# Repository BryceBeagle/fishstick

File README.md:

# fishstick
USB Dongle/adapter for gamecube controllers

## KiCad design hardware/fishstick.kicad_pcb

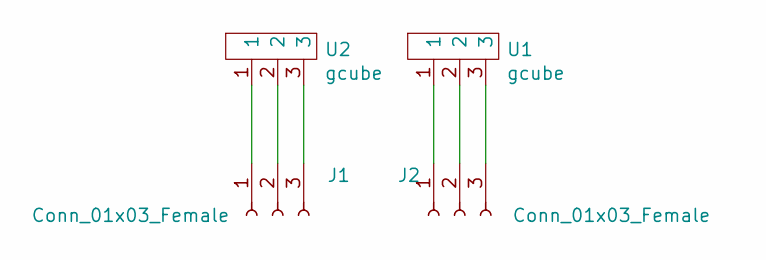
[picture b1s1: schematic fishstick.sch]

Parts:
J1, J2: Conn_01x03_Female; PinHeader_1x03_P2.54mm_Vertical
U1, U2: gcube; SOIC-3

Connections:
unnamed: J1.1, U2.1
unnamed: J1.2, U2.2
unnamed: J1.3, U2.3
unnamed: J2.1, U1.1
unnamed: J2.2, U1.2
unnamed: J2.3, U1.3

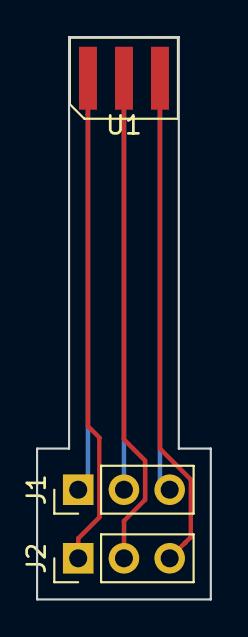
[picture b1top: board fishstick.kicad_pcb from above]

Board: 2 copper layers, 9.7 x 31.2 mm, 4 parts (1 on the bottom side), 6 nets.

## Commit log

2019-08-31 Initial commit of nested timer setup
2019-09-01 prepared directory for repository
2021-04-20 Switch to using rust
2022-01-29 Test bluepill flash light
2022-01-29 added intellij files
2022-01-29 added intellij rust run configurations
2022-01-29 added intellij items again
2022-01-29 newline dad
2022-01-29 removed run configs that contain absolute paths
2022-01-30 Add IntelliJ files and configuration (#1)
2022-01-30 added jet brains run configurations
2022-01-30 added run configurations
2022-01-30 new line youre welcome dad
2022-01-30 Add IntelliJ run configurations (#3)
2022-04-18 Rename project in `Cargo.toml` to `fishstick`
2022-04-18 Rename project in `Cargo.toml` to `fishstick` (#5)
2022-04-23 Update dependencies
    Resolves #6
2022-04-23 Update dependencies (#7)
2022-04-23 Add `bitvec` as a dependency
    Resolves #8
2022-04-23 Add `bitvec` as a dependency (#9)
    Resolves #8
2022-04-28 changed test code to use onboard LED instead of externally connected LEDs
2022-04-28 Fix name of binary in `Download and Run` run configuration
    Resolves #10
2022-04-28 Fix name of binary in `Download and Run` run configuration (#12)
2022-04-28 added newline
2022-04-28 changed test code to use onboard LED instead of externally connected LEDs (#11)
2022-05-08 Rename CLion project to `fishstick`
    Resolves #14
2022-05-08 Rename CLion project to `fishstick` (#15)
    Resolves #14
2022-07-23 Enhanced project structure for embedded software
    Resolves #16
2022-07-23 Enhanced project structure for embedded software (#17)
    Resolves #16
2022-07-23 switched main.rs to lib.rs and improved structure
2022-07-23 NEWLINE
2022-07-23 Switch `fishstick` crate from `main.rs` to `lib.rs` (#19)
2022-07-24 improved joybus method structure
2022-07-24 ignore .idea shelf
2022-07-24 Ignore `.idea` shelf (#26)
2022-07-24 Switch build run configuration to use `nightly` channel
    commit-id:3232d078
2022-07-24 Add missing space in `stm32` `Cargo.toml`
    Resolves #29
    commit-id:41f75ff2
2022-07-24 Use lowercase name for `build` run configuration
    commit-id:a68664fc
2022-07-24 Improve `joybus` method structure (#24)
2022-07-24 Add a `rust-toolchain.toml` to `fishstick` crate with nightly channel
    commit-id:3232d078
2022-07-24 Set `software/fishstick/tests` as a test source folder in CLion
    commit-id:5b14ba2b
2022-07-25 Use lowercase name for `build` run configuration (#31)
2022-07-25 Add missing space in `stm32` `Cargo.toml` (#33)
2022-07-25 Set `software/fishstick/tests` as a test source folder in CLion (#34)
2022-07-25 Stop using `nightly` channel for `stm32` crate
    Resolves #37
    commit-id:c3aac06d
2022-07-25 Stop using `nightly` channel for `stm32` crate (#38)
2022-07-25 implemented `Joybus` `send_receive` within trait itself and updated `Controller`
2022-07-25 switch to `pub mod joybus` since we are including everything already
2022-07-25 Revert "switch to `pub mod joybus` since we are including everything already"
    This reverts commit 24748f82f5f898f62dffec190a583538e391e744.
2022-07-25 added back `exists` method to `Controller`
2022-07-25 renamed `get_state` method to be more clear
2022-07-25 reverted to old `Controller` code as a next level abstraction for `Joybus`
2022-07-26 Implemented `Joybus` `send_receive`. Updated `Controller`. (#40)
2022-07-26 renamed stm32 crate to match specific device
2022-07-26 update `Cargo.lock`
2022-07-27 Rename `stm32` crate to match specific device (`stm32f103`) (#42)
2022-07-27 added `stm32f401` crate and dependencies
2022-07-27 changed run config parameters
2022-07-27 remove clippy pragma
2022-07-27 rename blackpill .cfg file
2022-07-27 remove errant comment
2022-07-28 rename run configurations; rename stlink config
    commit-id:8b618238
2022-07-28 un-rename stlink config
    commit-id:5cc6404f
2022-07-28 Add `stm32f401` crate and dependencies (#46)
2022-07-28 Bare deployment for `stm32f103` board
    Resolves #47
    Resolves #48
2022-07-28 Bare deployment for `stm32f103` board (#49)
2022-07-30 `fishstick-stm32f103` dependency on `fishstick`
    This makes the `fishstick-stm32f103` have a real dependency on the core
    `fishstick` crate
    Resolves #51
2022-07-30 `fishstick-stm32f103` dependency on `fishstick` (#52)
    This makes the `fishstick-stm32f103` have a real dependency on the core
    `fishstick` crate
    Resolves #51
2022-07-30 Sanity-check test for `fishstick` that runs on host machine
    Even though the test requires the `std` crate, the hardware crates can still use it at runtime.
    Resolves #53
2022-07-30 GitHub Linguist override for Linker Script files
    Resolves #50
2022-07-30 Sanity-check test for `fishstick` that runs on host machine (#54)
2022-07-30 GitHub Linguist override for Linker Script files (#55)
2022-11-05 remove nightly requirement
2022-11-05 use `panic_rtt_target` instead of `panic_halt`
2022-11-05 no test check to get rid of rust-analyzer error
2022-11-05 added `Embed.toml` for `cargo embed`
2022-11-05 added comment to explain rust-analyzer silence
2022-11-05 `cargo embed` setup for `stm-32f401` crate (#56)
2022-11-05 base for spi writing
2022-11-07 clock timing to fix weird SPI clock errors
2022-11-07 improved clock timing
2022-11-07 allow dead code on test message
2023-07-03 initial impl of a disgusting PWM DMA output
2023-08-12 Drop support for stm32f103
    Resolves #59
2023-08-12 Unpin and upgrade all dependency versions
    We can rely on the lockfile to keep the exact versions consistent
    Resolves #58
2023-08-12 DMA thing
2023-08-17 Drop support for stm32f103 (#60)
2023-08-20 update again
2023-08-20 fix unicode-ident checksum
2023-08-21 Switch logging from `rtt_target` to `defmt`
    Resolves #62
2023-08-26 Unpin and upgrade all dependency versions (#61)
2023-08-26 Replace all `stm32f401` configuration with `stm32f411` configuration
    Resolves #64
2023-08-26 Start using `embassy` framework
    Note that this introduces an issue where flashing requires using `BOOT0` and `NRST`
    Resolves #66
2023-10-01 Switch logging from `rtt_target` to `defmt` (#63)
2023-10-01 Replace `stm32f401` in run configuration with `stm32f411`
2023-10-01 Replace all `stm32f401` config with `stm32f411` config (#65)
2023-10-01 Start using `embassy` framework (#67)
2023-12-30 Bump all package versions
    Resolves #68
2023-12-30 Bump all package versions (#69)
    Resolves #68
2023-12-30 added `embassy-usb`, `futures` and updated dependencies
2023-12-30 added `embassy-usb`, `futures` and updated dependencies (#71)
2023-12-30 Working example of loopback over USB
    Plug in USBC and open Arduino Serial monitor. Anything sent over serial gets sent back in uppercase
2024-01-22 upload of usb mouse twitch test
2024-02-26 Add initial USB HID support
    This packet is completely wrong, but we'll fix that in a future PR.
    Resolves #72
2024-02-26 Upgrade all dependencies
    We can now unpin embassy from a git hash
    Resolves #75
2025-06-22 add initial flake
2025-06-22 update flake with relevant items
2025-06-22 add cargo workspace
2025-06-22 add flake lockfile
2025-06-22 use direnv
2025-06-22 add justfile
2025-06-22 update flake and get project in working state
2025-06-22 remove env rc
2025-06-22 remove justfile
2025-06-22 newlines
2025-06-22 Add nix flake for development (#79)
2025-06-24 add vscode to flake
2025-06-24 use stmf401 as as target chip
2025-06-24 add rhedgeco to authors
2025-06-24 add cargo expand
2025-06-24 remove old fishstick library
2025-06-24 update folder and package name
2025-06-24 fix workspace member
2025-06-24 Update project to use most recent embassy stuff (#81)
    updated all embassy stuff and use modern blinky example
    removed old fishstick library - should be reworked to be platform agnostic
    added vscode to flake - can be broken out and improved later
2025-07-23 [temp] Switch to features
2025-07-23 fix chip name feature association
2025-07-23 remove old `[default.rtt]`
2025-07-23 add justfile for easier command running
2025-07-23 ignore vscode settings
